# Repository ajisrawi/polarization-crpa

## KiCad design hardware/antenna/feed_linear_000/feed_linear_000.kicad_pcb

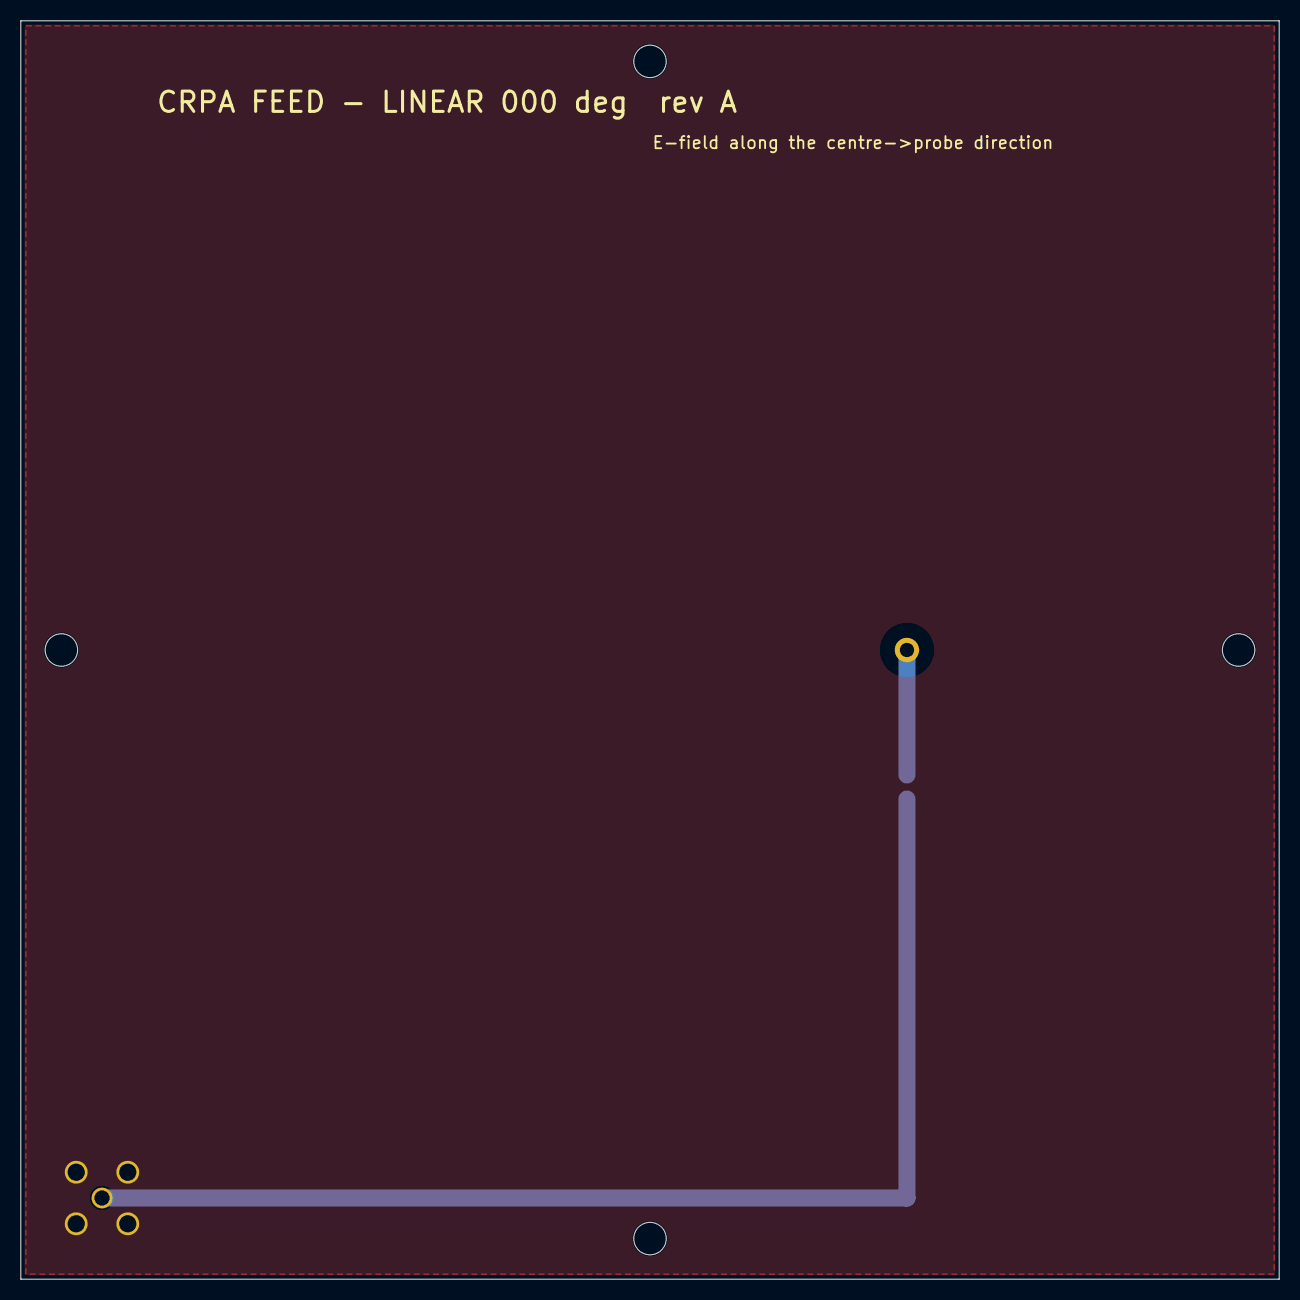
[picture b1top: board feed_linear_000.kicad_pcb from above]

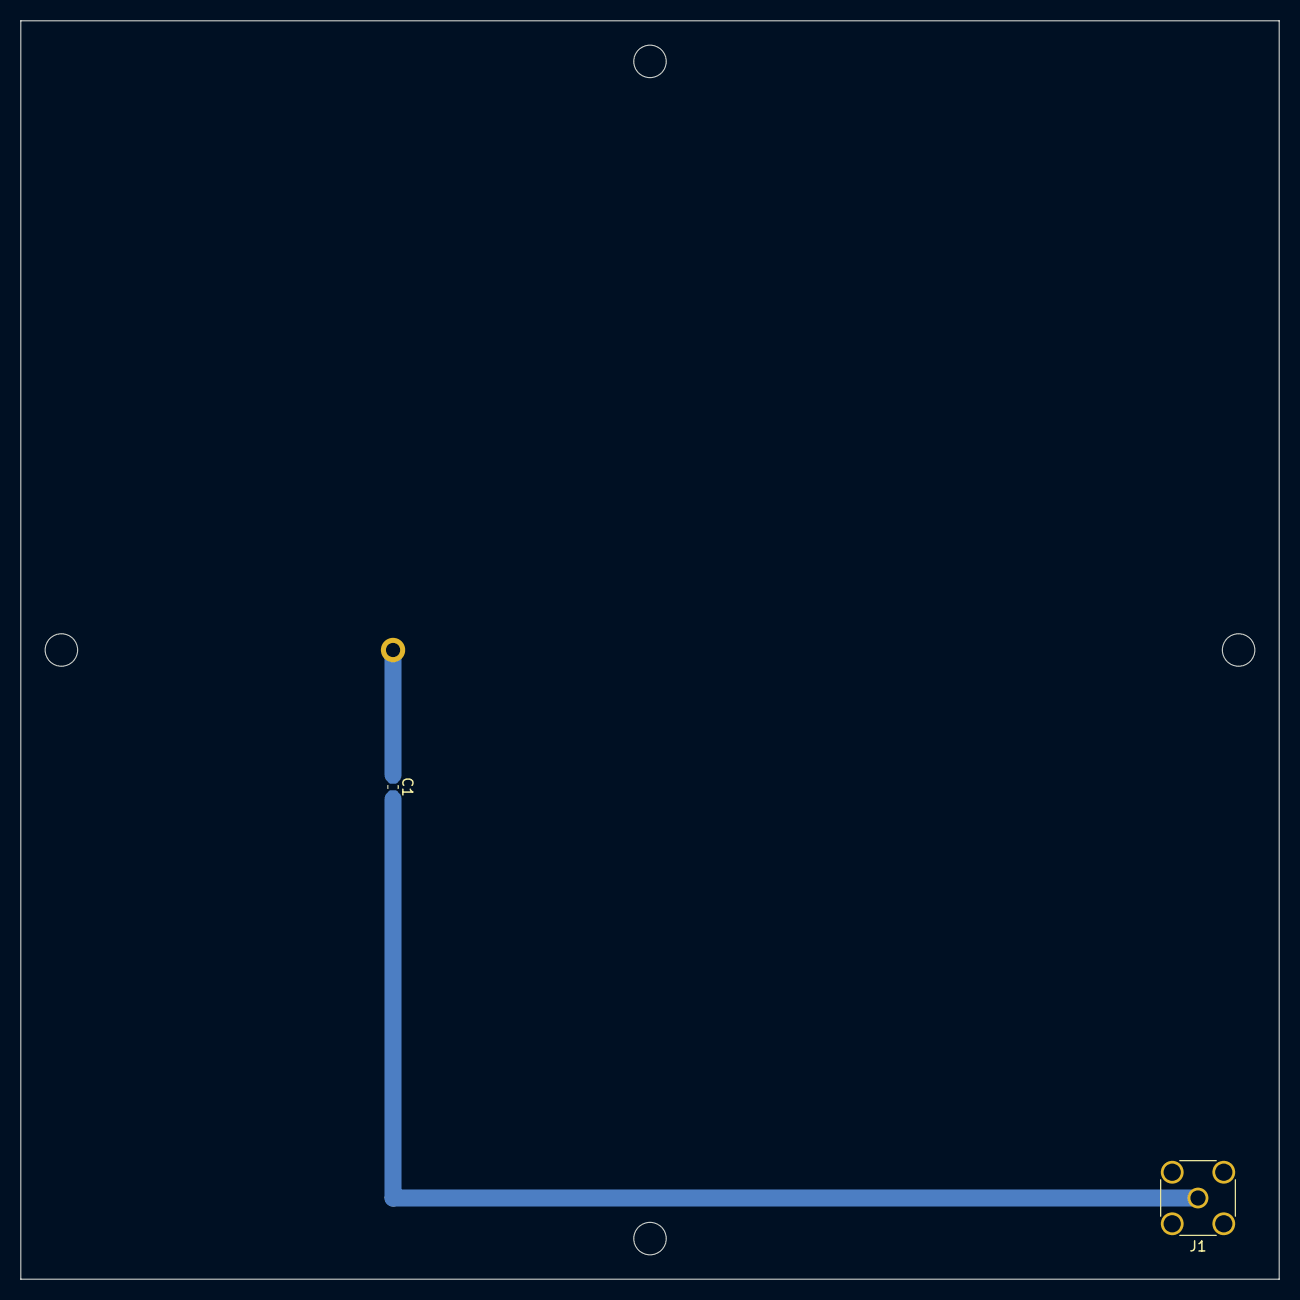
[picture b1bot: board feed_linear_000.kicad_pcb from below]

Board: 2 copper layers, 124.0 x 124.0 mm, 7 parts (2 on the bottom side), 2 nets.

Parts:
C1: 0R / ~2.2pF probe tune; C_0603_1608Metric
H1, H2, H3, H4: M3 nylon standoff; MountingHole_3.2mm_M3
J1: SMA vertical (Amphenol 132134); SMA_Amphenol_132134_Vertical
P1: probe

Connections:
PROBE: C1.1, P1.1
RF_OUT: C1.2, J1.1

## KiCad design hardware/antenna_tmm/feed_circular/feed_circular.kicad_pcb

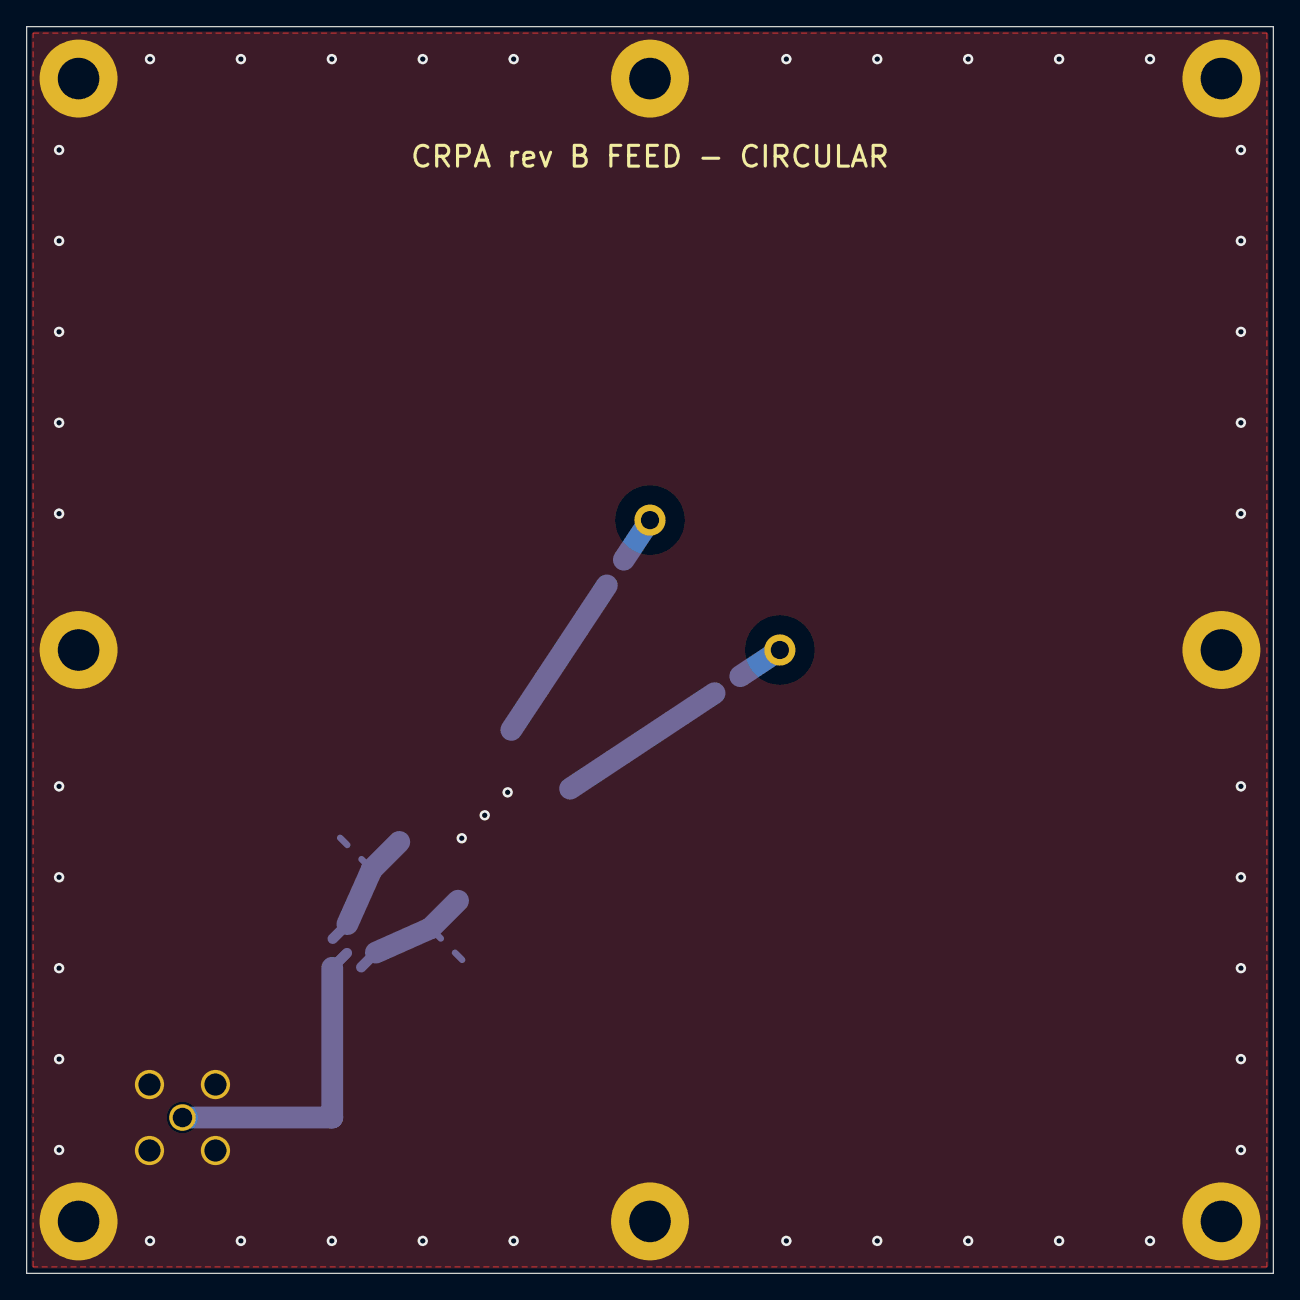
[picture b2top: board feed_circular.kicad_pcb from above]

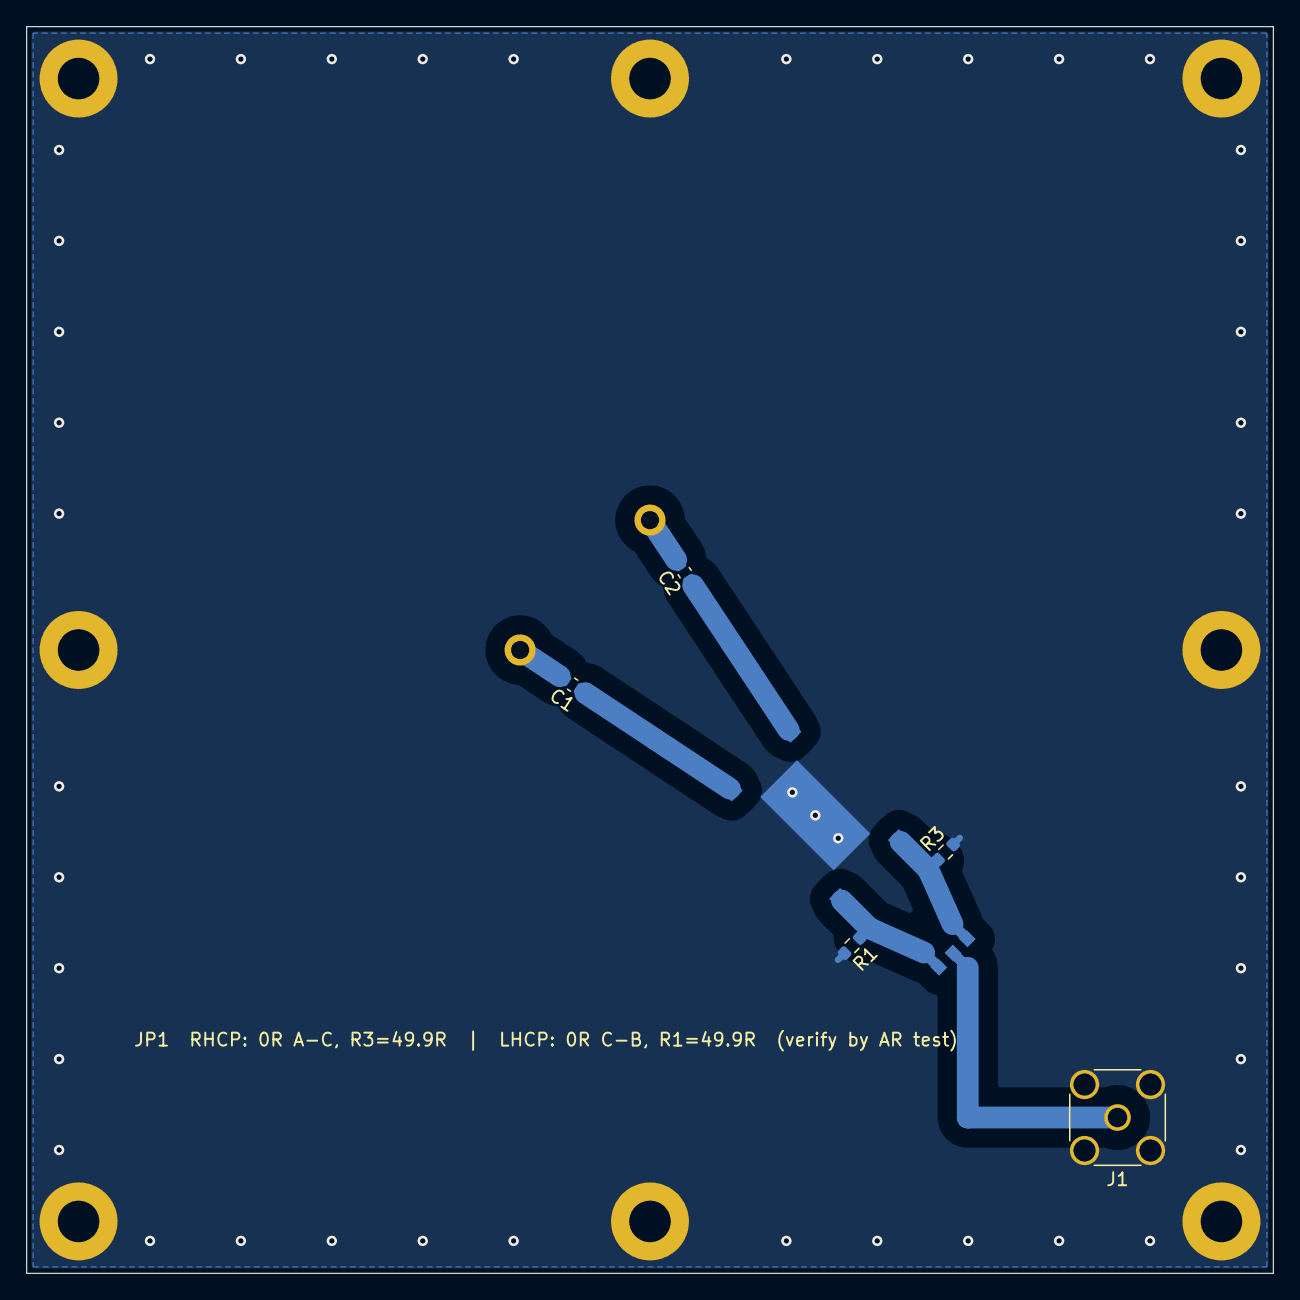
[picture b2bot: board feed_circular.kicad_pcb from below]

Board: 2 copper layers, 96.0 x 96.0 mm, 17 parts (7 on the bottom side), 8 nets.

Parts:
C1, C2: 0R (disk feed) / tune; C_0603_1608Metric
H1, H2, H3, H4, H5, H6, H7, H8: M3 plated hole for brass standoff to plate
J1: SMA vertical (Amphenol 132134); SMA_Amphenol_132134_Vertical
JP1: polarization select: 0R on A-C or C-B
P1, P2: probe
R1: 49.9R if RHCP not used, else DNP; R_0603_1608Metric
R3: 49.9R if LHCP not used, else DNP; R_0603_1608Metric
U1: Q3XG-1500R 90deg hybrid - LAND PATTERN PLACEHOLDE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

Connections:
GND: H1.1, H2.1, H3.1, H4.1, H5.1, H6.1, H7.1, H8.1, J1.2, R1.2, R3.2, U1.5
HYB1: JP1.B, R1.1, U1.1
HYB2: C1.1, U1.2
HYB3: C2.1, U1.3
HYB4: JP1.A, R3.1, U1.4
PROBE_P1: C1.2, P1.1
PROBE_P2: C2.2, P2.1
RF_OUT: J1.1, JP1.C
